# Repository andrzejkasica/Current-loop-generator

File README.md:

# Current-loop-generator
Hardware project of 2-wire current loop generator with additonal 2 relays controlled by STM32L433CCT6 with OLED display and incremental encoder.
Powered with external 24V power supply, projects uses buck converter for +5V line and LDO for +3V3

PCB front: 

Back of the PCB:

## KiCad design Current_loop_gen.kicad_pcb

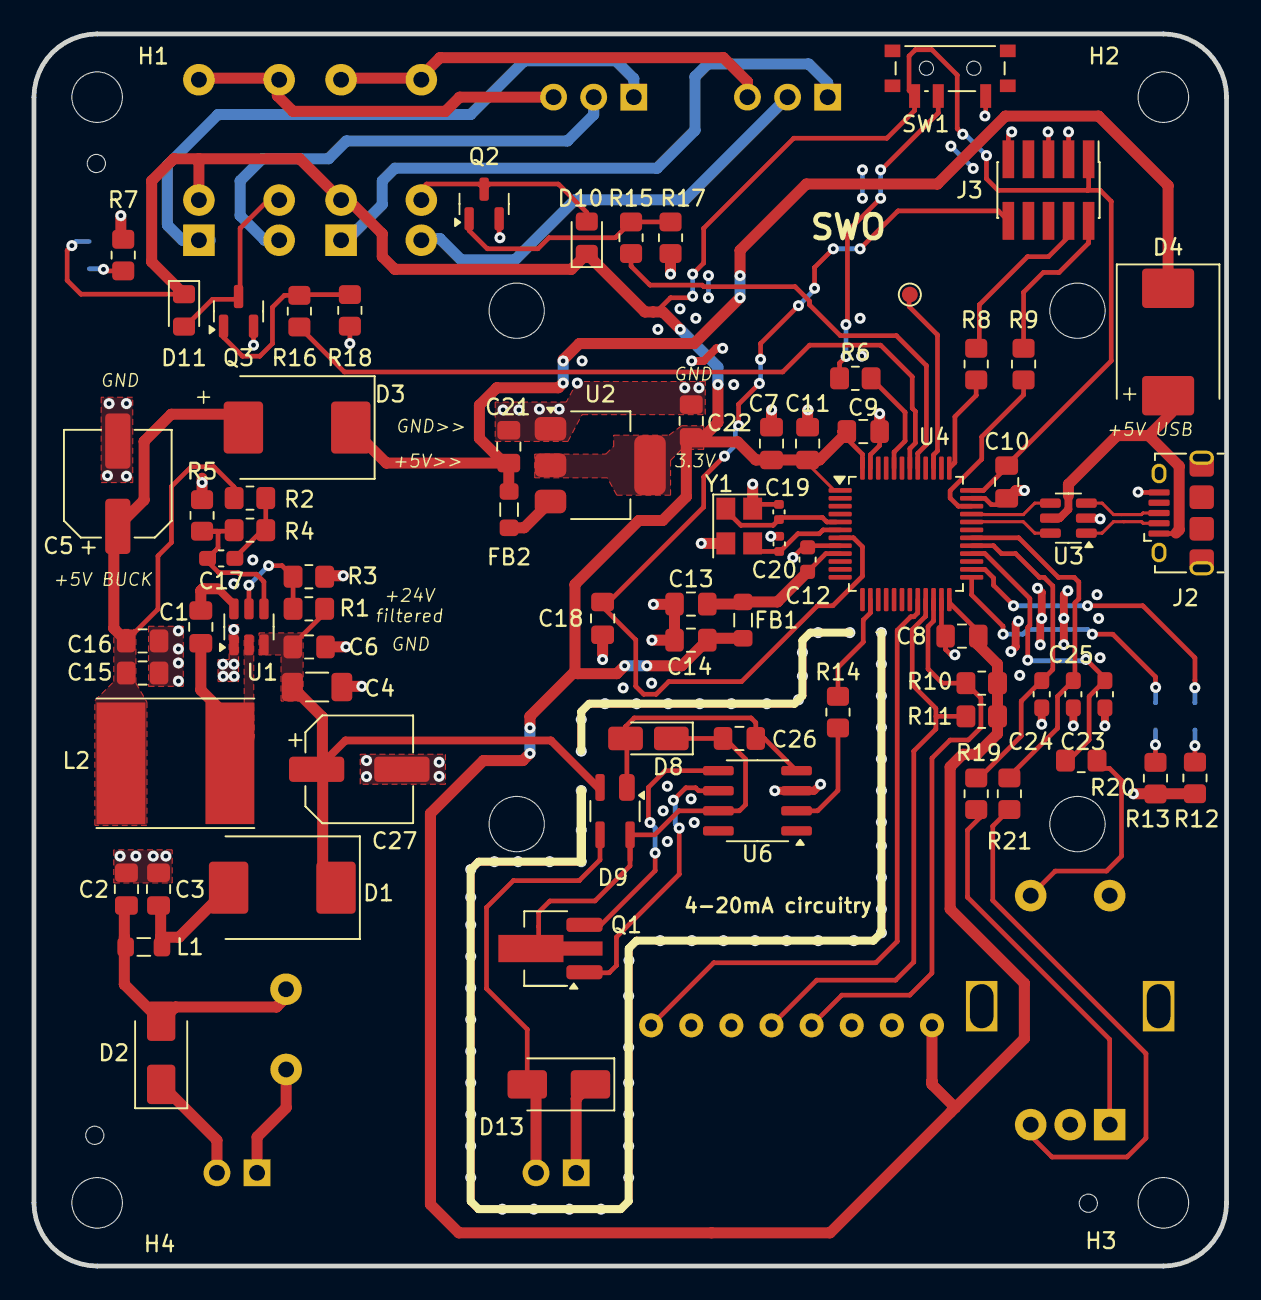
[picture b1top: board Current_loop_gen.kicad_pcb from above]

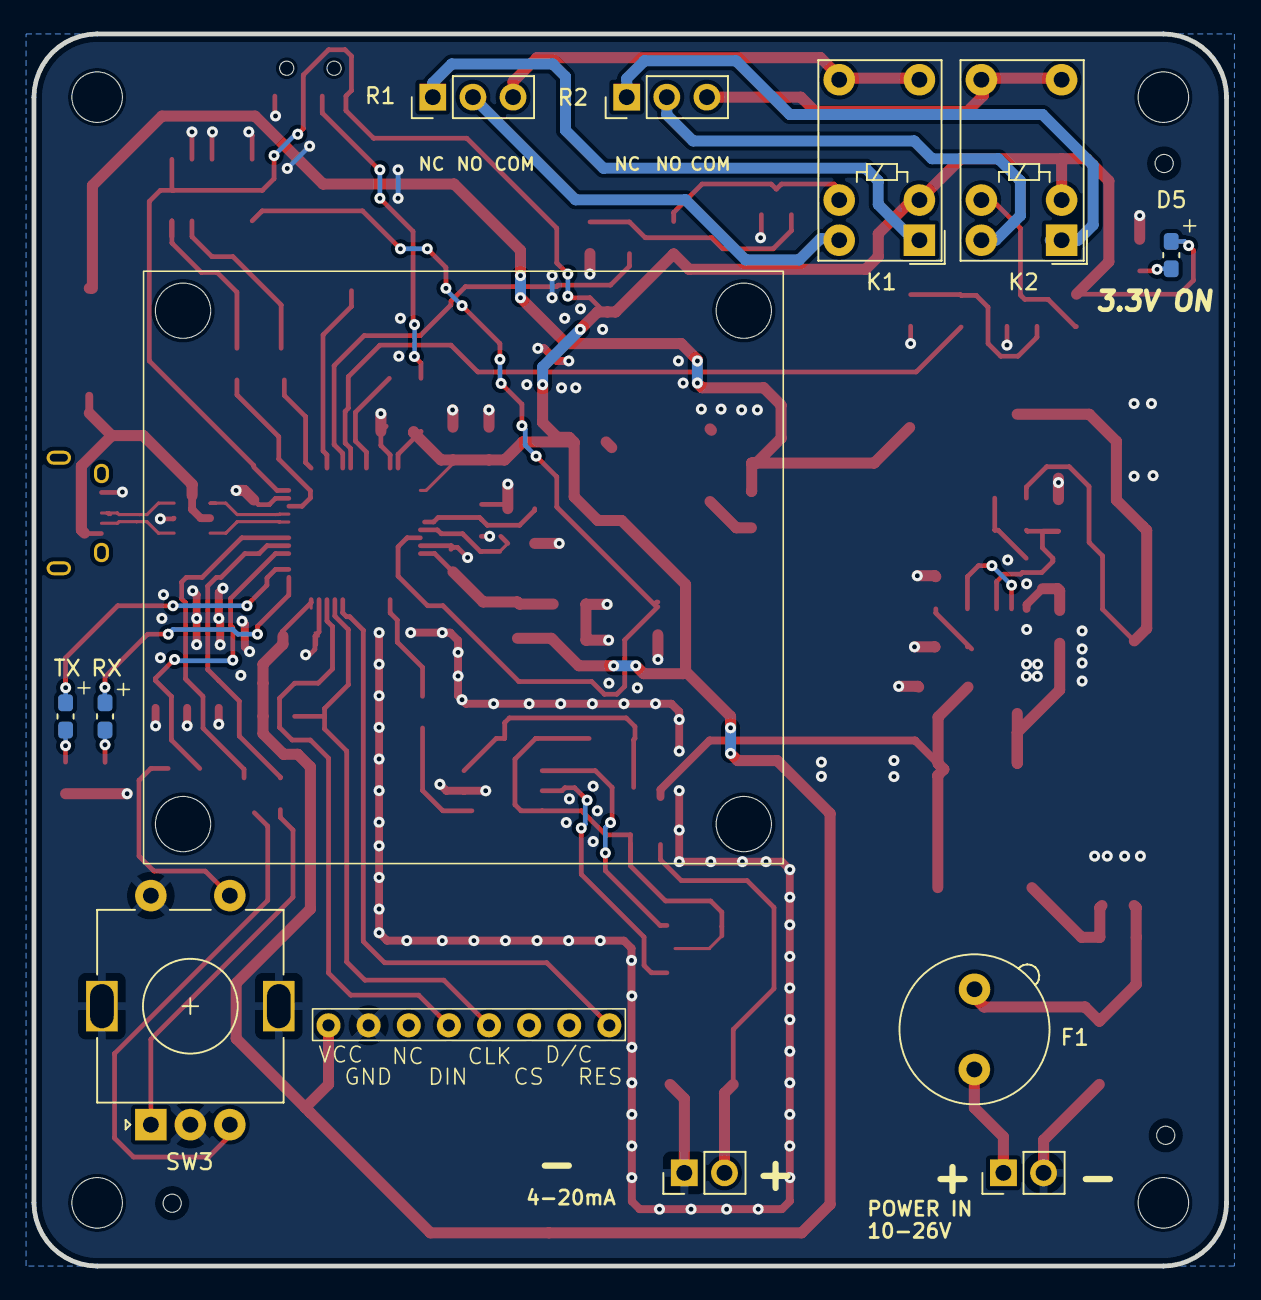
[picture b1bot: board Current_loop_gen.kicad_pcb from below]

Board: 2 copper layers, 75.5 x 78.0 mm, 90 parts (12 on the bottom side), 63 nets.

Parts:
C1, C2, C3, C6, C8, C9, C10, C11, C18, C26: 100n; C_0805_2012Metric_Pad1.18x1.45mm_HandSolder
C4: 22u; C_1206_3216Metric_Pad1.33x1.80mm_HandSolder
C5, C27: 47u; CP_Elec_6.3x5.8
C7: 10u; C_0805_2012Metric_Pad1.18x1.45mm_HandSolder
C12: 10n; C_0603_1608Metric
C13, C14: 1u; C_0805_2012Metric_Pad1.18x1.45mm_HandSolder
C15, C16, C21, C22: 22u; C_0805_2012Metric_Pad1.18x1.45mm_HandSolder
C17: 75p; C_0603_1608Metric_Pad1.08x0.95mm_HandSolder
C19, C20: 10p; C_0402_1005Metric
C23, C24, C25: 10n; C_0603_1608Metric_Pad1.08x0.95mm_HandSolder
D1: B340; D_SMC
D2, D13: SMAJ30CA; D_SMA
D3, D4: SX33L_R1; D_SMC
D5: RED; C_0603_1608Metric_Pad1.08x0.95mm_HandSolder
D6: BLUE; C_0603_1608Metric_Pad1.08x0.95mm_HandSolder
D7: GREEN; C_0603_1608Metric_Pad1.08x0.95mm_HandSolder
D8: 1N47xxA; D_MicroMELF_Handsoldering
D9: BAS4002ARPPE6327; SOT-143_Handsoldering
D10, D11: 1N4148; D_0805_2012Metric_Pad1.15x1.40mm_HandSolder
F1: Fuse_Small; Fuseholder_TR5_Littelfuse_No560_No460
FB1: 120R; L_0805_2012Metric_Pad1.05x1.20mm_HandSolder
FB2: 100 @ 100MHz; L_0805_2012Metric_Pad1.05x1.20mm_HandSolder
H1, H2, H3, H4: MountingHole; MountingHole_3.2mm_M3_DIN965
J1: Power 24V; PinHeader_1x02_P2.54mm_Vertical
J2: USB_B_Micro; USB_Micro-B_Amphenol_10118194-0001LF_Horizontal
J3: SWD Debug; PinHeader_2x05_P1.27mm_Vertical_SMD
J4: Current loop out; PinHeader_1x02_P2.54mm_Vertical
J5, J6: Conn_01x03; PinHeader_1x03_P2.54mm_Vertical
K1, K2: G5V-1; Relay_SPDT_Omron_G5V-1
L1: 120R; L_0805_2012Metric_Pad1.05x1.20mm_HandSolder
L2: 10u; L_Taiyo-Yuden_NR-80xx_HandSoldering
Q1: FCE690; SOT-89-3_Handsoldering
Q2, Q3: DMN65D8L-7; SOT-23
R1: 511k; R_0805_2012Metric_Pad1.20x1.40mm_HandSolder
R2: 49k9; R_0805_2012Metric_Pad1.20x1.40mm_HandSolder
R3: 105k; R_0805_2012Metric_Pad1.20x1.40mm_HandSolder
R4: 100k; R_0805_2012Metric_Pad1.20x1.40mm_HandSolder
R5: 13k3; R_0805_2012Metric_Pad1.20x1.40mm_HandSolder
R6: 10k; R_0805_2012Metric_Pad1.20x1.40mm_HandSolder
R7, R10, R11, R12, R13, R15, R16: 1k5; R_0805_2012Metric_Pad1.20x1.40mm_HandSolder
R8, R9: 100; R_0805_2012Metric_Pad1.20x1.40mm_HandSolder
R14: 15k; R_0805_2012Metric_Pad1.20x1.40mm_HandSolder
R17, R18: 150k; R_0805_2012Metric_Pad1.20x1.40mm_HandSolder
R19, R20, R21: 10K; R_0805_2012Metric_Pad1.20x1.40mm_HandSolder
SW1: SW_SPDT; SW_SPDT_PCM12
SW3: RotaryEncoder_Switch_MP; RotaryEncoder_Alps_EC11E-Switch_Vertical_H20mm
TP1: TestPoint; TestPoint_Pad_D1.0mm
U1: TPS54302; SOT-23-6
U2: AMS1117-3.3; SOT-223-3_TabPin2
U3: USBLC6-2SC6; SOT-23-6
U4: STM32L433CCTx; LQFP-48_7x7mm_P0.5mm
U5: WSH-10451; wsh-10451
U6: XTR116U; SOIC-8_3.9x4.9mm_P1.27mm
Y1: 16MHz; Crystal_SMD_3225-4Pin_3.2x2.5mm

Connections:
+3.3V: C7.1, C8.1, C9.1, C10.1, C11.1, C14.1, C22.1, D5.2 (A), D10.1 (K), D11.1 (K), FB1.2, J3.1, K1.2, K2.2, R10.1, R11.1, SW1.3 (C), U2.2 (VO), U4.1 (VBAT), U4.24 (VDD), U4.36 (VDDUSB), U4.48 (VDD), U5.8 (VCC)
+3.3VA: C12.1, C13.1, FB1.1, U4.9 (VDDA)
+5VTPS: C5.1, C15.1, C16.1, D3.2 (A), L2.2, R2.1
+24V: C4.1, C6.1, C27.1, D1.1 (K), D9.2, R1.1, U1.3 (VIN)
/ALARM1: R15.1, U4.41 (PB5)
/ALARM2: R16.1, U4.42 (PB6)
/BOOT0: R6.2, U4.44 (PH3)
/Buck_BOOT: C1.1, U1.6 (BOOT)
/Buck_EN: R1.2, R3.1, U1.5 (EN)
/Buck_FB: C17.2, R4.2, R5.1, U1.4 (FB)
/Buck_SW: C1.2, L2.1, U1.2 (SW)
/DAC1_OUT1: R14.1, U4.14 (PA4)
/DAC1_XTR_IN: R14.2, U6.2 (IIN)
/HSE_IN: C19.1, U4.5 (PH0), Y1.1
/HSE_OUT: C20.1, U4.6 (PH1), Y1.3
/I2C2_SCL: R11.2, U4.21 (PB10), U5.4 (CLK)
/I2C2_SDA: R10.2, U4.22 (PB11), U5.5 (DIN)
/LED_BLUE: D6.2 (A), U4.26 (PB13)
/LED_GREEN: D7.2 (A), U4.25 (PB12)
/NRST: C18.1, J3.10, U4.7 (NRST)
/PWR_LED_K: D5.1 (K), R7.1
/R1_COM: J5.3, K1.5, K1.6
/R1_NC: J5.1, K1.1
/R1_NO: J5.2, K1.10
/R2_COM: J6.3, K2.5, K2.6
/R2_NC: J6.1, K2.1
/R2_NO: J6.2, K2.10
/RE_S_A: C24.1, R19.1, U4.29 (PA8)
/RE_S_B: C25.1, R21.1, U4.30 (PA9)
/RE_S_SW: C23.1, R20.2, U4.28 (PB15)
/SWCLK: R8.2, U4.37 (PA14)
/SWDIO: R9.1, U4.34 (PA13)
/SWO: TP1.1, U4.39 (PB3)
/USB_CONN_DP+: J2.3 (D+), U3.3 (I/O2)
/USB_CONN_DP-: J2.2 (D-), U3.1 (I/O1)
/USB_DP+: U3.4 (I/O2), U4.33 (PA12)
/USB_DP-: U3.6 (I/O1), U4.32 (PA11)
/WSH_RST: U4.20 (PB2), U5.1 (RES)
/XTR_IO: C26.2, D8.2 (A), D9.1 (-), U6.4 (IO)
/XTR_VPLUS: C26.1, D8.1 (K), D9.4 (+), Q1.2 (C), U6.7 (V+)
GND: C2.2, C3.2, C4.2, C5.2, C6.2, C7.2, C8.2, C9.2, C10.2, C11.2, C12.2, C13.2, C14.2, C15.2, C16.2, C18.2, C19.2, C20.2, C21.2, C22.2, C23.2, C24.2, C25.2, C27.2, D2.1 (A1), D13.1 (A1), J1.2, J2.5 (GND), J3.3, J3.5, J3.9, J4.1, Q2.2 (S), Q3.2 (S), R3.2, R5.2, R7.2, R12.2, R13.2, R17.1, R18.1, SW1.1 (A), SW3.C, SW3.MP, SW3.S2, U1.1 (GND), U2.1 (GND), U3.2 (GND), U4.8 (VSSA), U4.23 (VSS), U4.35 (VSS), U4.47 (VSS), U5.7 (GND), U6.3 (IRET), Y1.2, Y1.4
unnamed: C17.1, R2.2, R4.1
unnamed: C3.1, D1.2 (A), L1.2
unnamed: C2.1, D2.2 (A2), F1.2, L1.1
unnamed: D6.1 (K), R12.1
unnamed: D7.1 (K), R13.1
unnamed: D10.2 (A), K1.9, Q2.3 (D)
unnamed: D11.2 (A), K2.9, Q3.3 (D)
unnamed: D9.3, D13.2 (A2), J4.2
unnamed: J3.2, R9.2
unnamed: J3.4, R8.1
unnamed: Q1.1 (B), U6.6 (B)
unnamed: Q1.3 (E), U6.5 (E)
unnamed: Q2.1 (G), R15.2, R17.2
unnamed: Q3.1 (G), R16.2, R18.2
unnamed: R19.2, SW3.A
unnamed: R20.1, SW3.S1
unnamed: R21.2, SW3.B
unnamed: R6.1, SW1.2 (B)
unnamed: FB2.2, U2.3 (VI)
VBUS: C21.1, D3.1 (K), D4.1 (K), FB2.1
VBUS_USB: D4.2 (A), J2.1 (VBUS), U3.5 (VBUS)
VDC: F1.1, J1.1

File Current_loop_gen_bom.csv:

"Reference","Value","Datasheet","Footprint","Qty","DNP","JLCPCB Part #"
"C12,C23,C24,C25","10n","~","-- różne wartości --","4","","C57112"
"C1,C2,C3,C6,C8,C9,C10,C11,C18,C26","100n","~","Capacitor_SMD:C_0805_2012Metric_Pad1.18x1.45mm_HandSolder","10","","C49678"
"C15,C16,C21,C22","22u","~","Capacitor_SMD:C_0805_2012Metric_Pad1.18x1.45mm_HandSolder","4","","C45783"
"C19,C20","10p","~","Capacitor_SMD:C_0402_1005Metric","2","","C32949"
"C13,C14","1u","~","Capacitor_SMD:C_0805_2012Metric_Pad1.18x1.45mm_HandSolder","2","","C28323"
"R4","100k","~","Resistor_SMD:R_0805_2012Metric_Pad1.20x1.40mm_HandSolder","1","","C25741"
"R14","15k","~","Resistor_SMD:R_0805_2012Metric_Pad1.20x1.40mm_HandSolder","1","","C17475"
"R17,R18","150k","~","Resistor_SMD:R_0805_2012Metric_Pad1.20x1.40mm_HandSolder","2","","C17470"
"R19,R20,R21","10K","~","Resistor_SMD:R_0805_2012Metric_Pad1.20x1.40mm_HandSolder","3","","C17414"
"R6","10k","~","Resistor_SMD:R_0805_2012Metric_Pad1.20x1.40mm_HandSolder","1","","C17414"
"R8,R9","100","~","Resistor_SMD:R_0805_2012Metric_Pad1.20x1.40mm_HandSolder","2","","C17408"
"Y1","16MHz","~","Crystal:Crystal_SMD_3225-4Pin_3.2x2.5mm","1","","C13738"
"U2","AMS1117-3.3","http://www.advanced-monolithic.com/pdf/ds1117.pdf","Package_TO_SOT_SMD:SOT-223-3_TabPin2","1","","C6186"
"FB1,L1","120R","~","Inductor_SMD:L_0805_2012Metric_Pad1.05x1.20mm_HandSolder","2","","C5671"
"R7,R10,R11,R12,R13,R15,R16","1k5","~","Resistor_SMD:R_0805_2012Metric_Pad1.20x1.40mm_HandSolder","7","","C4310"
"C17","75p","~","Capacitor_SMD:C_0603_1608Metric_Pad1.08x0.95mm_HandSolder","1","","C1671"
"FB2","100 @ 100MHz","~","Inductor_SMD:L_0805_2012Metric_Pad1.05x1.20mm_HandSolder","1","","C1015"

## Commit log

2025-01-28 Commiting hardware project
2025-01-28 Production files
    Manufacturing and assembly files for JLCPCB, some parts were assembly separately
